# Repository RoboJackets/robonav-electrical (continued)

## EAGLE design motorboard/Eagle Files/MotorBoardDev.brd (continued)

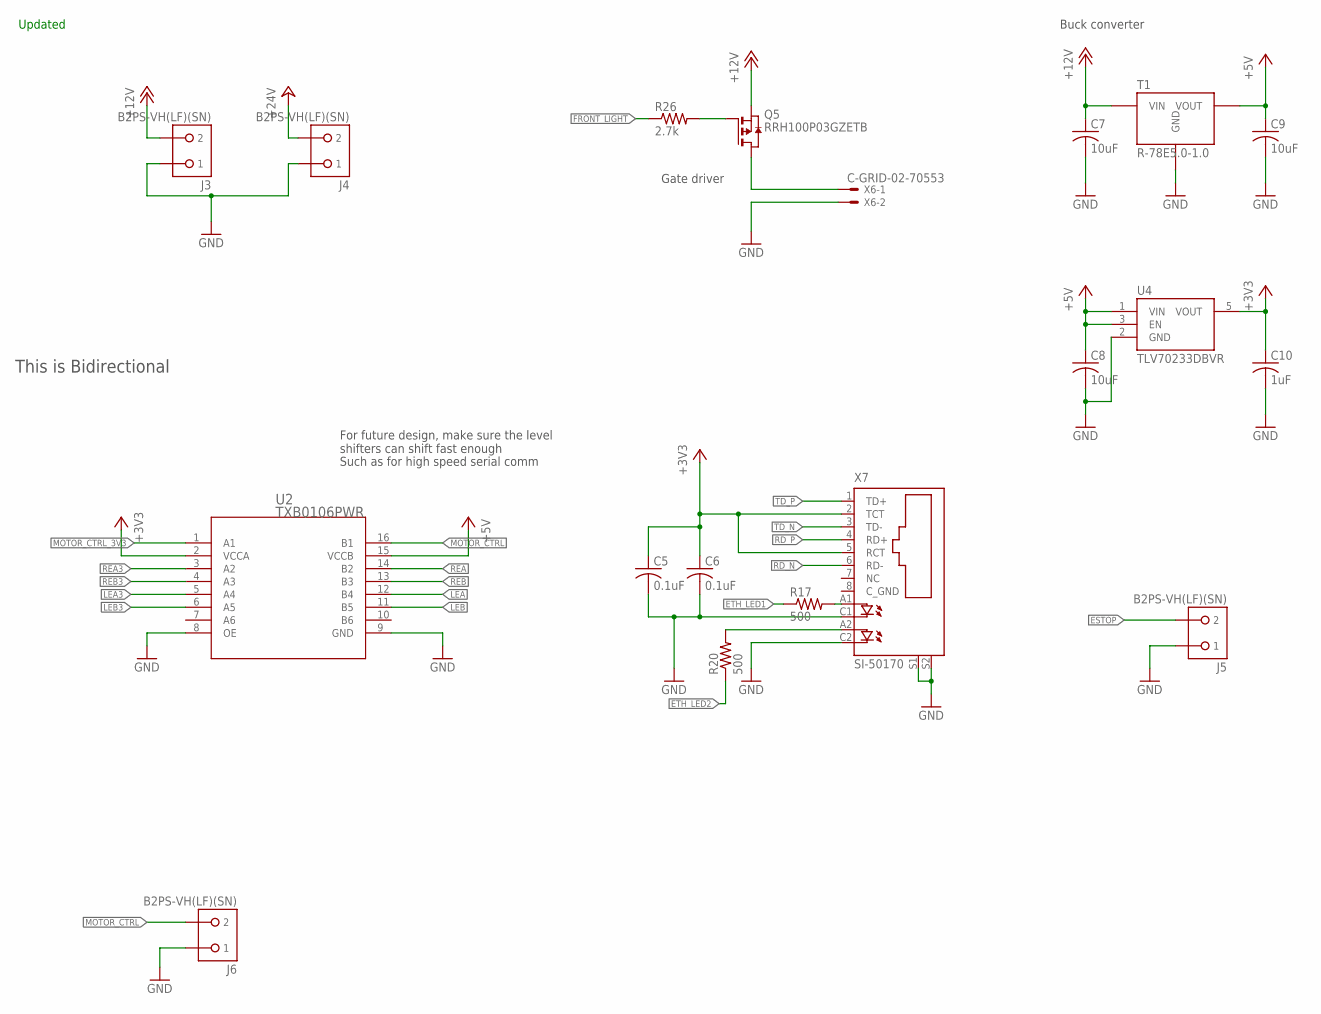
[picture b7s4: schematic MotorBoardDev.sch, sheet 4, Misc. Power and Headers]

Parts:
C5, C6: 0.1uF; C0603
C7, C8, C9: 10uF; C0805
C10: 1uF; C0805
J3, J4, J5, J6: B2PS-VH(LF)(SN); B2PS-CENTERED
Q5: RRH100P03GZETB; SOIC-8
R17, R20: 500; R0603
R26: 2.7k; R0603
T1: R-78E5.0-1.0; R-78E
U2: TXB0106PWR; PW16
U4: TLV70233DBVR; SOT-23-5
X6: C-GRID-02-70553; 70553-02
X7: SI-50170

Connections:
+3V3: C5.1, C6.1, C10.1, U2.2 (VCCA), U4.5 (VOUT), X7.2 (TCT), X7.5 (RCT); also elsewhere on the board
+5V: C8.1, C9.1, T1.3 (VOUT), U2.15 (VCCB), U4.1 (VIN), U4.3 (EN); also elsewhere on the board
+12V: C7.1, J3.2, Q5.1 (S), Q5.2 (S), Q5.3 (S), T1.1 (VIN); also elsewhere on the board
+24V: J4.2; also elsewhere on the board
ESTOP: J5.2; also elsewhere on the board
ETH_LED1: R17.1; also elsewhere on the board
ETH_LED2: R20.1; also elsewhere on the board
FRONT_HDR: Q5.5 (D), Q5.6 (D), Q5.7 (D), Q5.8 (D), X6.1
FRONT_LIGHT: R26.1; also elsewhere on the board
FRONT_R: Q5.4 (G), R26.2
GND: C5.2, C6.2, C7.2, C8.2, C9.2, C10.2, J3.1, J4.1, J5.1, J6.1, T1.2 (GND), U2.8 (OE), U2.9 (GND), U4.2 (GND), X6.2, X7.C1 (C), X7.C2 (C1), X7.S1, X7.S2; also elsewhere on the board
LEA: U2.12 (B4); also elsewhere on the board
LEA3: U2.5 (A4); also elsewhere on the board
LEB: U2.11 (B5); also elsewhere on the board
LEB3: U2.6 (A5); also elsewhere on the board
MOTOR_CTRL: J6.2, U2.16 (B1)
MOTOR_CTRL_3V3: U2.1 (A1); also elsewhere on the board
unnamed: R17.2, X7.A1 (A)
unnamed: R20.2, X7.A2 (A1)
RD_N: X7.6 (RD-); also elsewhere on the board
RD_P: X7.4 (RD+); also elsewhere on the board
REA: U2.14 (B2); also elsewhere on the board
REA3: U2.3 (A2); also elsewhere on the board
REB: U2.13 (B3); also elsewhere on the board
REB3: U2.4 (A3); also elsewhere on the board
TD_N: X7.3 (TD-); also elsewhere on the board
TD_P: X7.1 (TD+); also elsewhere on the board

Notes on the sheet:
Buck converter
This is Bidirectional
Updated
Gate driver
For future design, make sure the level shifters can shift fast enough
Such as for high speed serial comm

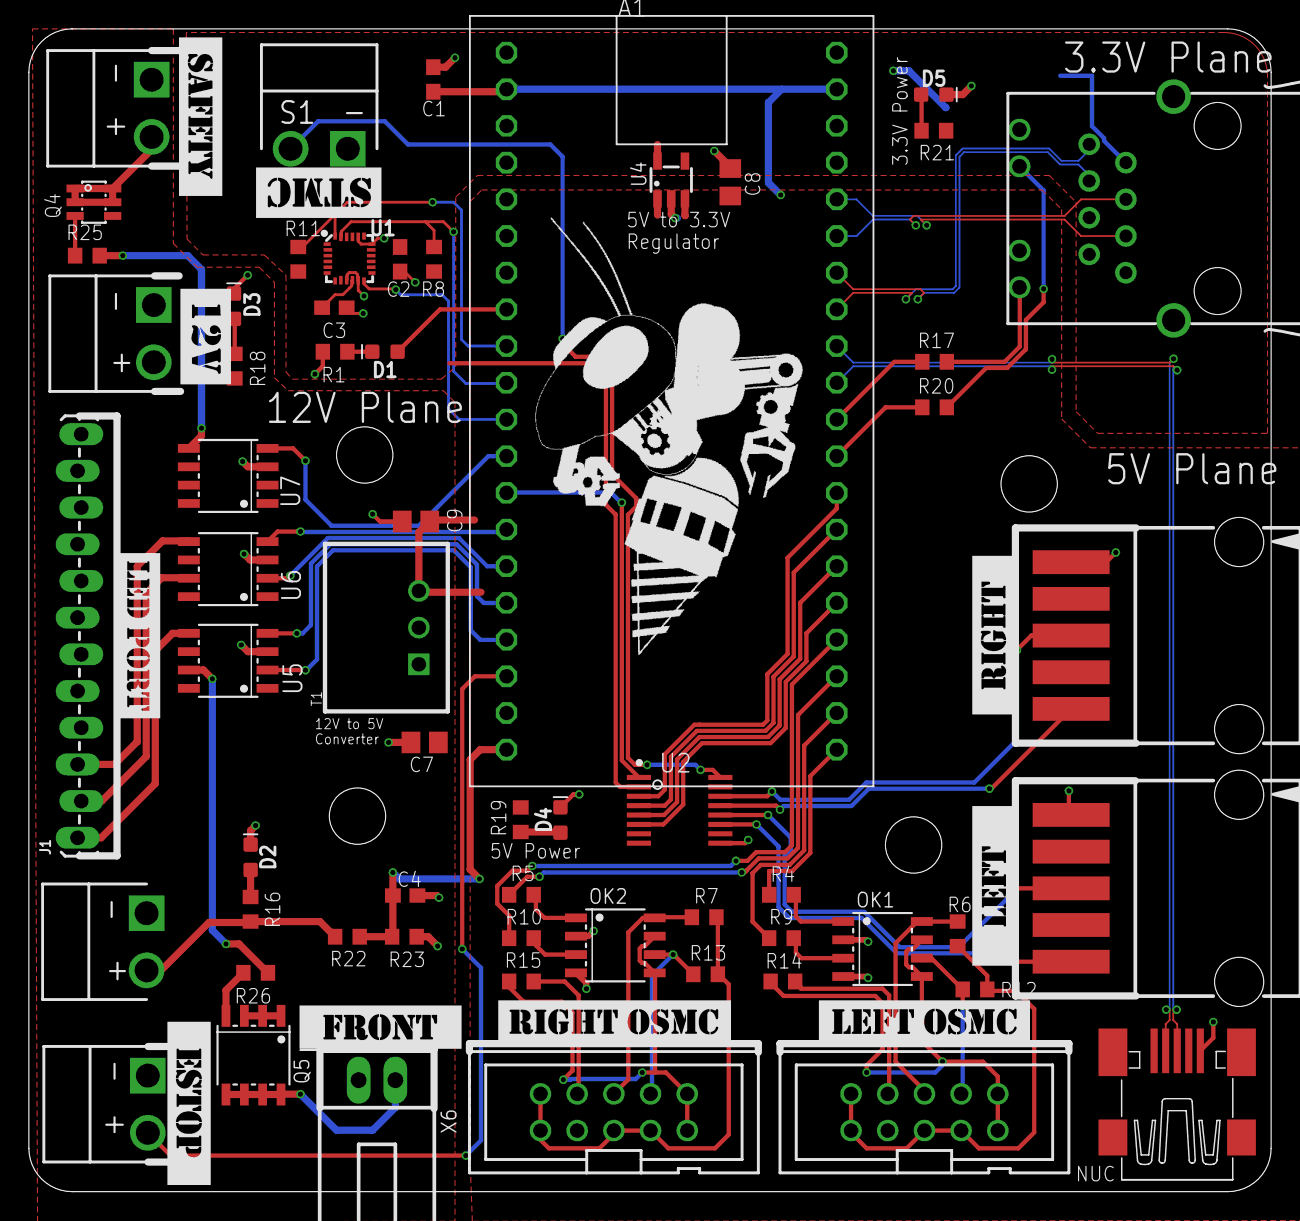
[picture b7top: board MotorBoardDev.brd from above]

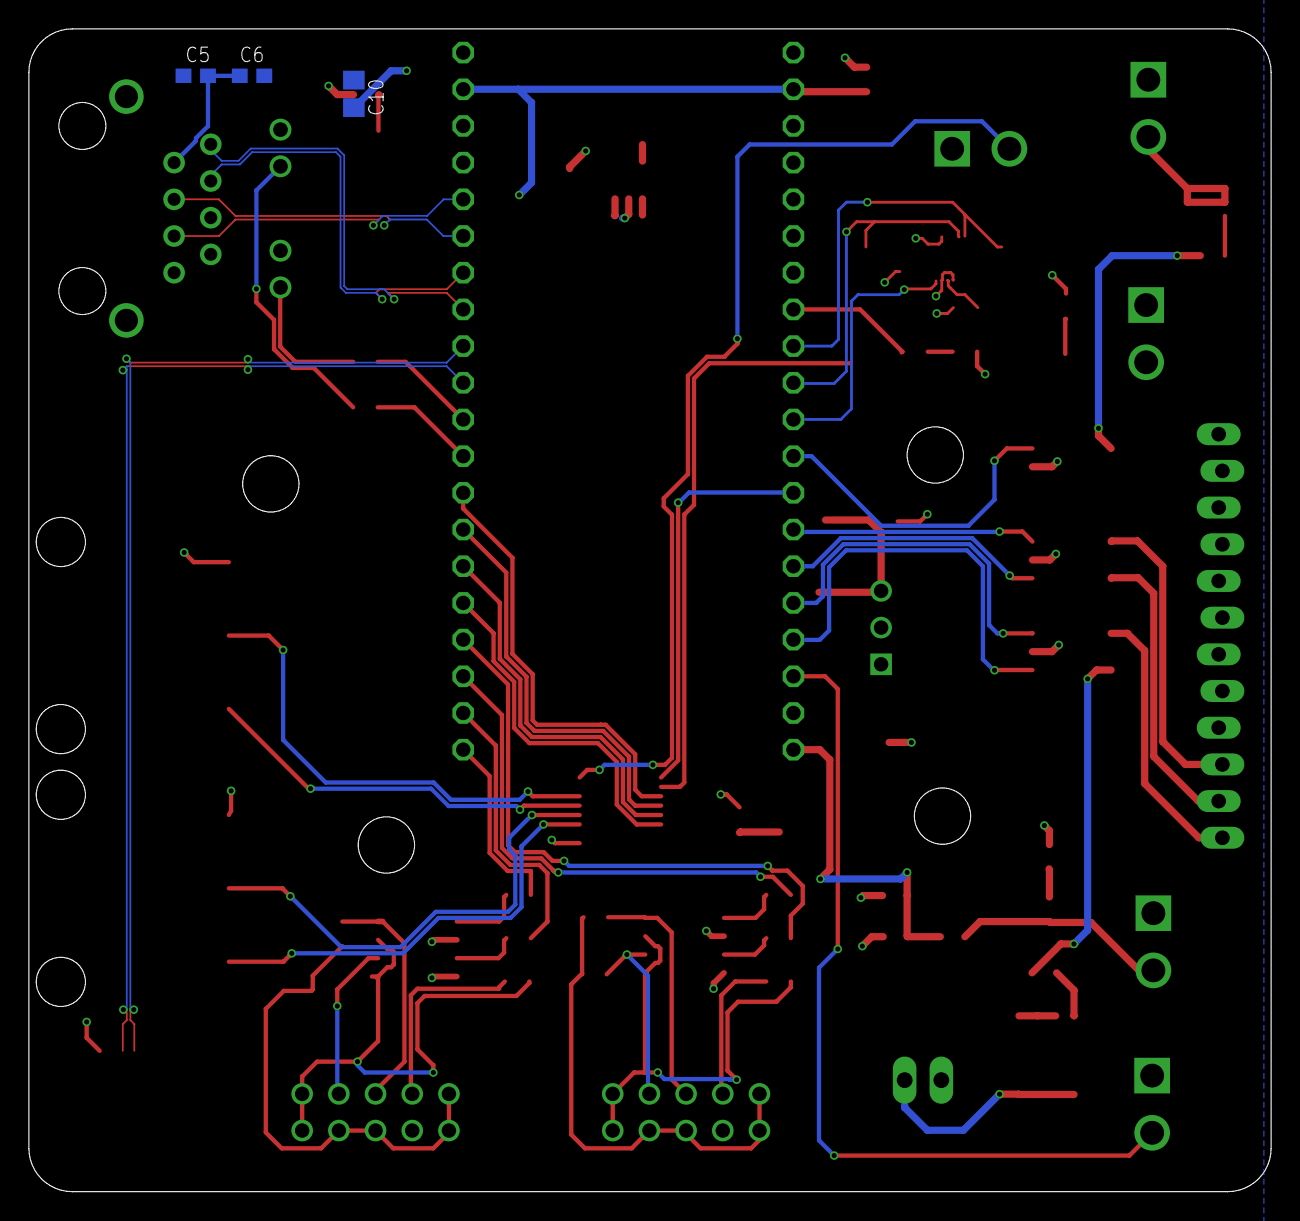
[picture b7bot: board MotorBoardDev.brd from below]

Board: 2 copper layers, 86.0 x 80.5 mm, 79 parts (3 on the bottom side), 69 nets.

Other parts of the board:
U$1, U$2, U$3, U$4: STANDOFF-HOLE
U$5: 12V
U$6: 24V
U$7: LEFTOSMC
U$8: RIGHTOSMC
U$9: LEDPORT
U$10: ROBOBUZZ_1.4X
U$11: ESTOP
U$12: SAFETY
U$13: LEFT
U$14: RIGHT
U$15: FRONT
U$16: STMC
